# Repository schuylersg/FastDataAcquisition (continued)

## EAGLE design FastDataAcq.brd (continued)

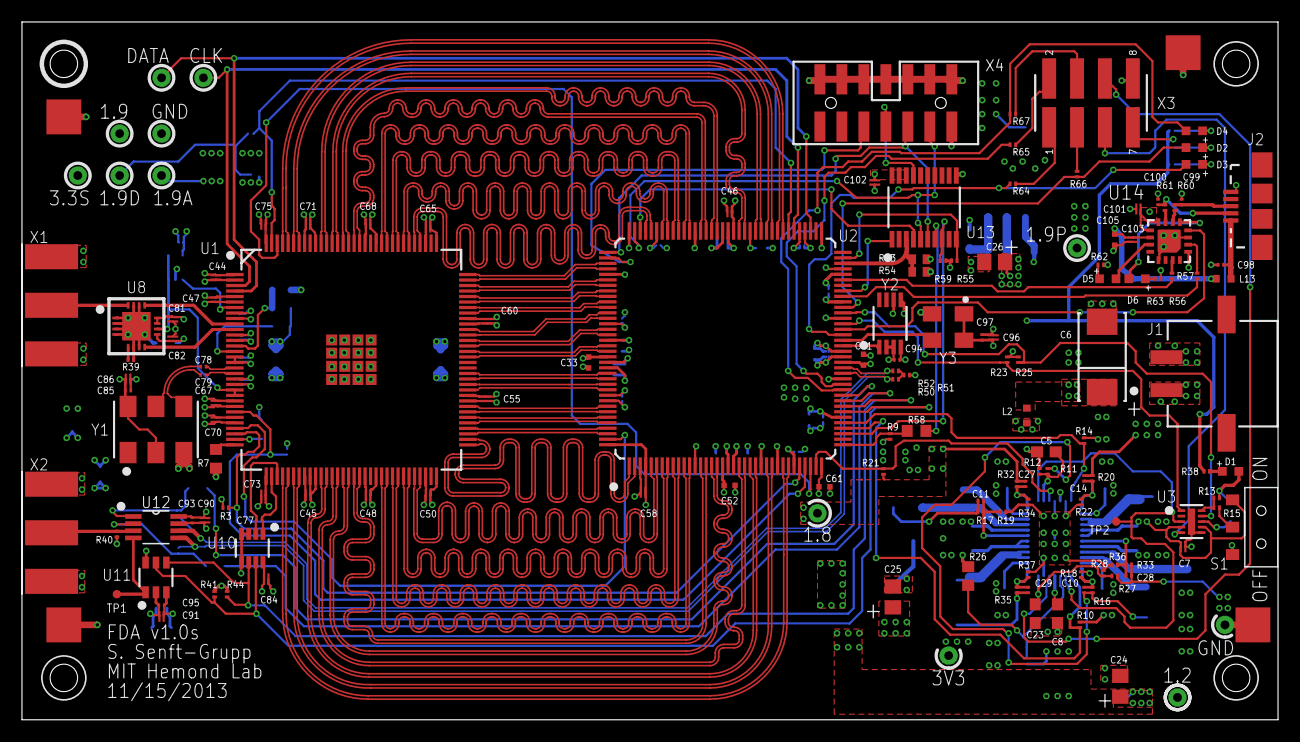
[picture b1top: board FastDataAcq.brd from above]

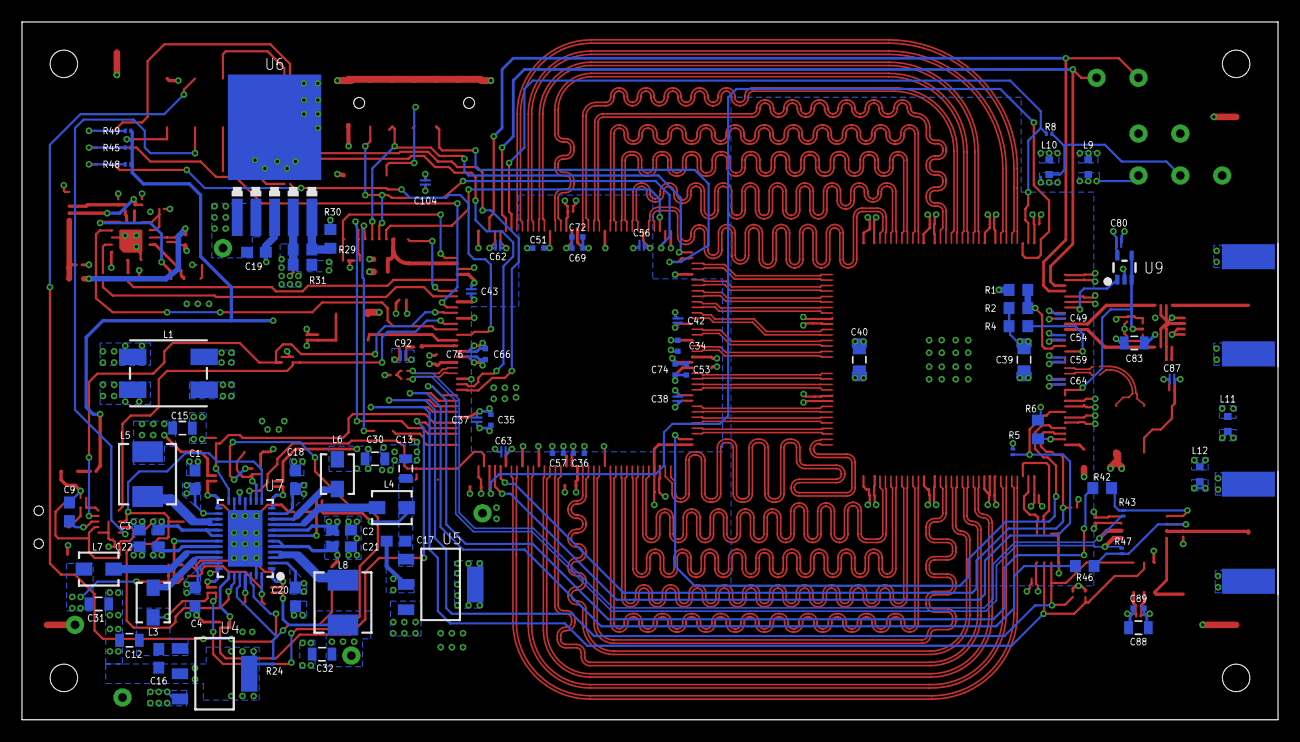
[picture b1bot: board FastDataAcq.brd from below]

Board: 4 copper layers, 114.3 x 63.5 mm, 225 parts (82 on the bottom side), 186 nets.

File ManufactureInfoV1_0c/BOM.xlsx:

Parts | Value | MFG PN | Digikey PN | SUPPLIER | Qty | Package | Description
C1, C2, C3, C4, C8, C16, C17, C18, C19, C20, C21, C22 | 10uF |  | 445-4112-1-ND | DIGIKEY | 12 | C0603 | CAPACITOR, European symbol
C10, C11, C14, C27, C28, C29 | 10pF |  | 445-1769-1-ND | DIGIKEY | 6 | C0201 | CAPACITOR, European symbol
C12, C13, C15, C30, C31, C32, C39, C40, C83, C88 | 33uF |  | 445-8238-1-ND | DIGIKEY | 10 | 805 | Capacitor
C24, C25, C26 | 22uF 150mOhm ESR |  | P16231CT-ND | DIGIKEY | 3 | C0805 | CAPACITOR, American symbol
C33, C34, C35, C36, C41, C51, C52, C53, C57, C61, C66, C69, C72, C74, C89, C105 | 4.7uF | CL05A475MQ5NRNC | 1276-1056-1-ND | DIGIKEY | 16 | 0402_C | Capacitors.
C37, C38, C42, C43, C46, C56, C58, C62, C63, C76 | 0.47uF |  | 1276-1779-1-ND | DIGIKEY | 10 | 0204REVERSE | Capacitors.
C5, C9, C23 | DNP |  |  |  | 3 | C0603 | CAPACITOR, European symbol
C6 | 100uF | ECASD91B107M012K00 | 490-5480-1-ND | DIGIKEY | 1 | 2917_MURATA_CAP | Polarized capacitors.
C7, C44, C45, C47, C48, C49, C50, C54, C55, C59, C60, C64, C65, C67, C68, C70, 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 | .1uF |  | 587-2152-1-ND | DIGIKEY | 30 | 0204REVERSE | Capacitors.
C77 | 100pF |  | 445-4675-1-ND | DIGIKEY | 1 | C0201 | CAPACITOR, European symbol
C78, C79 | 4.7nF |  | 445-13726-1-ND | DIGIKEY | 2 | C0201 | CAPACITOR, European symbol
C85, C93, C94, C95, C97, C98 | 10nF |  | 445-1793-1-ND | DIGIKEY | 6 | C0201 | CAPACITOR, European symbol
C87, C90, C104 | 1uF |  | 445-9091-1-ND | DIGIKEY | 3 | 0204REVERSE | Capacitors.
C99, C100 | 47pF |  | 445-1782-1-ND | DIGIKEY | 2 | C0201 | CAPACITOR, European symbol
D1, D4 | LED_0603_RED |  | LNJ237W82RACT-ND | DIGIKEY | 2 | 0603_LED | LED.
D2, D6 | LED_0603_BLUE | LTST-C193TBKT-5A | 160-1827-1-ND | DIGIKEY | 2 | 0603_LED | LED.
D3, D5 | LED_0603_GREEN | LTST-C193KGKT-5A | 160-1828-1-ND | DIGIKEY | 2 | 0603_LED | LED.
J1 | MICRO-FIT_3.0_2POS_RA_SMD | 436500212 | WM1890CT-ND | DIGIKEY | 1 | MICRO-FIT_3.02POS_RA_SMD
J2 | USB_MICROAB_SMT | 10104111-0001LF | 609-4053-1-ND | DIGIKEY | 1 | USB_MICROAB_SMT_1 | USB Connector
L1 | CHOKE_CM_ACM7060-301 | ACM7060-301-2PL-TL01 | 445-2214-1-ND | DIGIKEY | 1 | ACM7060_CHOKE | Common mode choke.
L13 | 330 | BLM18SG331TN1D | 490-3997-1-ND | DIGIKEY | 1 | MURATA_BLM18 | Ferrite bead.
L2, L9, L10, L11, L12 | 26 | BLM18SG260TN1D | 490-3995-1-ND | DIGIKEY | 5 | MURATA_BLM18 | Ferrite bead.
L3, L4, L6, L7 | 2.2uH |  | 541-1322-1-ND | DIGIKEY | 4 | 3.0X3.6_VISHAY | Inductors.
L5, L8 | 2.2uH |  | 541-1220-1-ND | DIGIKEY | 2 | 5.18X5.49_VISHAY | Inductors.
R1, R2, R4, R6, R26 | DNP |  |  |  | 5 | R0603 | RESISTOR, American symbol
R10, R13, R14, R16, R17, R20, R23, R24, R25 | 523K |  | P523KABCT-ND | DIGIKEY | 9 | R0201 | RESISTOR, American symbol
R11, R34 | 649K |  | P649KABCT-ND | DIGIKEY | 2 | R0201 | RESISTOR, American symbol
R12, R19 | 150K |  | 1276-3719-1-ND | DIGIKEY | 2 | R0201 | RESISTOR, American symbol
R15 | 113k |  | P113KABCT-ND | DIGIKEY | 1 | R0201 | RESISTOR, American symbol
R18, R28, R33 | 210K |  | P210KABCT-ND | DIGIKEY | 3 | R0201 | RESISTOR, American symbol
R22 | 280K |  | P280KABCT-ND | DIGIKEY | 1 | R0201 | RESISTOR, American symbol
R27, R37 | 270k |  | P270KABCT-ND | DIGIKEY | 2 | R0201 | RESISTOR, American symbol
R29 | 1.15k 1% | RC1608F1151CS | 1276-4649-1-ND | DIGIKEY | 1 | R0603 | RESISTOR, American symbol
R3, R5, R8, R21, R41, R43, R44, R47 | 10k | RC0603J103CS | 1276-3817-1-ND | DIGIKEY | 8 | R0201 | RESISTOR, American symbol
R30 | 2k 1% | RC1608F202CS | 1276-3495-1-ND | DIGIKEY | 1 | R0603 | RESISTOR, American symbol
R31 | 100 | RC1608J101CS | 1276-5038-1-ND | DIGIKEY | 1 | R0603 | RESISTOR, American symbol
R32 | 806K |  | P806KABCT-ND | DIGIKEY | 1 | R0201 | RESISTOR, American symbol
R35 | 845k |  | P845KABCT-ND | DIGIKEY | 1 | R0201 | RESISTOR, American symbol
R36 | 422K |  | P442KABCT-ND | DIGIKEY | 1 | R0201 | RESISTOR, American symbol
R38, R45, R48, R49, R55, R56, R57, R62, R63, R64, R65, R66, R67 | 330 | RC0603J331CS | 1276-3787-1-ND | DIGIKEY | 13 | R0201 | RESISTOR, American symbol
R39, R40, R50, R51, R52 | 50 | RC0603F49R9C | 1276-3590-1-ND | DIGIKEY | 5 | R0201 | RESISTOR, American symbol
R42 | 26.1k |  | 1276-4779-1-ND | DIGIKEY | 1 | R0603 | RESISTOR, American symbol
R46 | 16k |  | 1276-5091-1-ND | DIGIKEY | 1 | R0603 | RESISTOR, American symbol
R53, R54 | 100 0.1% | ERA-2AEB101X | P100DCCT-ND | DIGIKEY | 2 | R0402 | RESISTOR, American symbol
R58 | 0 |  | 311-0.0GRCT-ND | DIGIKEY | 1 | R0603 | RESISTOR, American symbol
R60, R61 | 27 |  | 1276-3577-1-ND | DIGIKEY | 2 | R0201 | RESISTOR, American symbol
R7 | 3.3k 0.1% |  | P3.3KDBCT-ND | DIGIKEY | 1 | R0603 | RESISTOR, American symbol
R9, R59 | 4.7k | ERJ-1GNJ472C | P4.7AECT-ND | DIGIKEY | 2 | R0201 | RESISTOR, American symbol
S1 | SLIDER_SPDT_AYZ0102AGRLC | AYZ0102AGRLC | 401-2012-1-ND | DIGIKEY | 1 | AYZ0102AGRLC | SPDT Slider switch from C&K Corp.
U1 | ADC08D500 | ADC08D500CIYB/NOPB | ADC08D500CIYB/NOPB-ND | DIGIKEY | 1 | 128HLQFP | TI ADC08D500 is a dual ADC running at 500MHz for a total of 1 GSPS. Verified=fa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
U10 | TMP421 | TMP421AIDCNT | 296-21990-1-ND | DIGIKEY | 1 | SOT23-8 | Remote and local temperature sensor (+/- 1C) from TI. TMP421. http://www.ti.com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
U11 | DAC101C081 | DAC101C081CIMK/NOPB | DAC101C081CIMK/NOPBCT-ND | DIGIKEY | 1 | SOT23-6 | 10-bit DAC from TI. http://www.ti.com/lit/ds/symlink/dac101c081.pdf
U12 | ADCMP553BRMZ | ADCMP553BRMZ | ADCMP553BRMZ-ND | DIGIKEY | 1 | SOP65P490X110-8N | PECL/LVPECL Comparators
U13 | XCFXXS04 | XCF04SVOG20C | 122-1288-5-ND | DIGIKEY | 1 | TSSOP20_XILINX | XCFxxS Xilinx Program Flash.
U14 | FT230XQ | FT230XQ-R | 768-1130-1-ND | DIGIKEY | 1 | QFN16 | USB to BASIC UART IC
U2 | XC6SLX9-3TQG144C | XC6SLX9-3TQG144C | 122-1747-ND | DIGIKEY | 1 | TQG144 | Xilinx Spartan 6 LX9 FPGA in the TQG144 package.
U3 | LTC2955-1 | LTC2955CDDB-1#TRMPBF | LTC2955CDDB-1#TRMPBFCT-ND | DIGIKEY | 1 | 10-DFN | Pushbutton On/Off Controller with Automatic Turn-On
U4 | LT1963AEST-2.5 | LT1963AEST-2.5#PBF | LT1963AEST-2.5#PBF-ND | DIGIKEY | 1 | SOT223 | LT1963A Series LDO in a 3 Lead SOT223 package. http://cds.linear.com/docs/en/da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
U5 | LT1963AEST-3.3 | LT1963AEST-3.3#PBF | LT1963AEST-3.3#PBF-ND | DIGIKEY | 1 | SOT223 | LT1963A Series LDO in a 3 Lead SOT223 package. http://cds.linear.com/docs/en/da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
U6 | LT1963AEQ | LT1963AEQ#PBF | LT1963AEQ#PBF-ND | DIGIKEY | 1 | Q5-DD | LT1963 1.5A, Low Noise, Fast Transient Response LDO Regulator
U7 | LTC3374QFN | TC3374EUHF#PBF | LTC3374EUHF#PBF-ND | DIGIKEY | 1 | 38-QFN_(5X7) | LTC3374 8-Channel 1A Buck DC-DC Regulator. http://cds.linear.com/docs/en/datash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
U8 | LMH6555 | LMH6555SQ/NOPB | LMH6555SQ/NOPBCT-ND | DIGIKEY | 1 | 16WQFN | LMH6555 is a low distortion 1.2 GHz differential driver. It can be configured f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
U9 | LMV321SC-70 | LMV321IDCKR | 296-9568-1-ND | DIGIKEY | 1 | SC-70 | LMV321 Low Voltage Rail-to-rail op amp from TI. Verified=false.
X1, X2 | SMA-142-0701-801/806 | 142-0701-801 | J502-ND | DIGIKEY | 2 | J502-ND-142-0701-801/806 | SMA 50 Ohm End Launch Jack Receptacle - Round Contact
X3 | HEADER_0.1_8P_2R_SMT" | 15912080 | WM17450-ND | DIGIKEY | 1 | HEADER_8P_2R_SMT
X4 | 87832-14 | 878321420 | WM18641-ND | DIGIKEY | 1 | 87832-14 | Milli-Grid Header
Y1 | SI530-500 | 530FC500M000DG | 530FC500M000DG | SILICON LABS | 1 | SI530 | Crystal Oscillator from Silicon Labs. Factory progrramed between 0.01 and 1.4 G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
Y2 | 100MHz | DS1088LU-100+ | DS1088LU-100+-ND | DIGIKEY | 1 | UMAX8 | MAXIM DS1088L Fixed frequency EconOscillator. Factory programmed between 321kHz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
Y3 | DNP | 500SAAA-ACF | 500SAAA-ACF-ND | DIGIKEY | 1 | SI500S | Silicon Labs SI500S programmable oscillator. https://www.silabs.com/Support%20D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

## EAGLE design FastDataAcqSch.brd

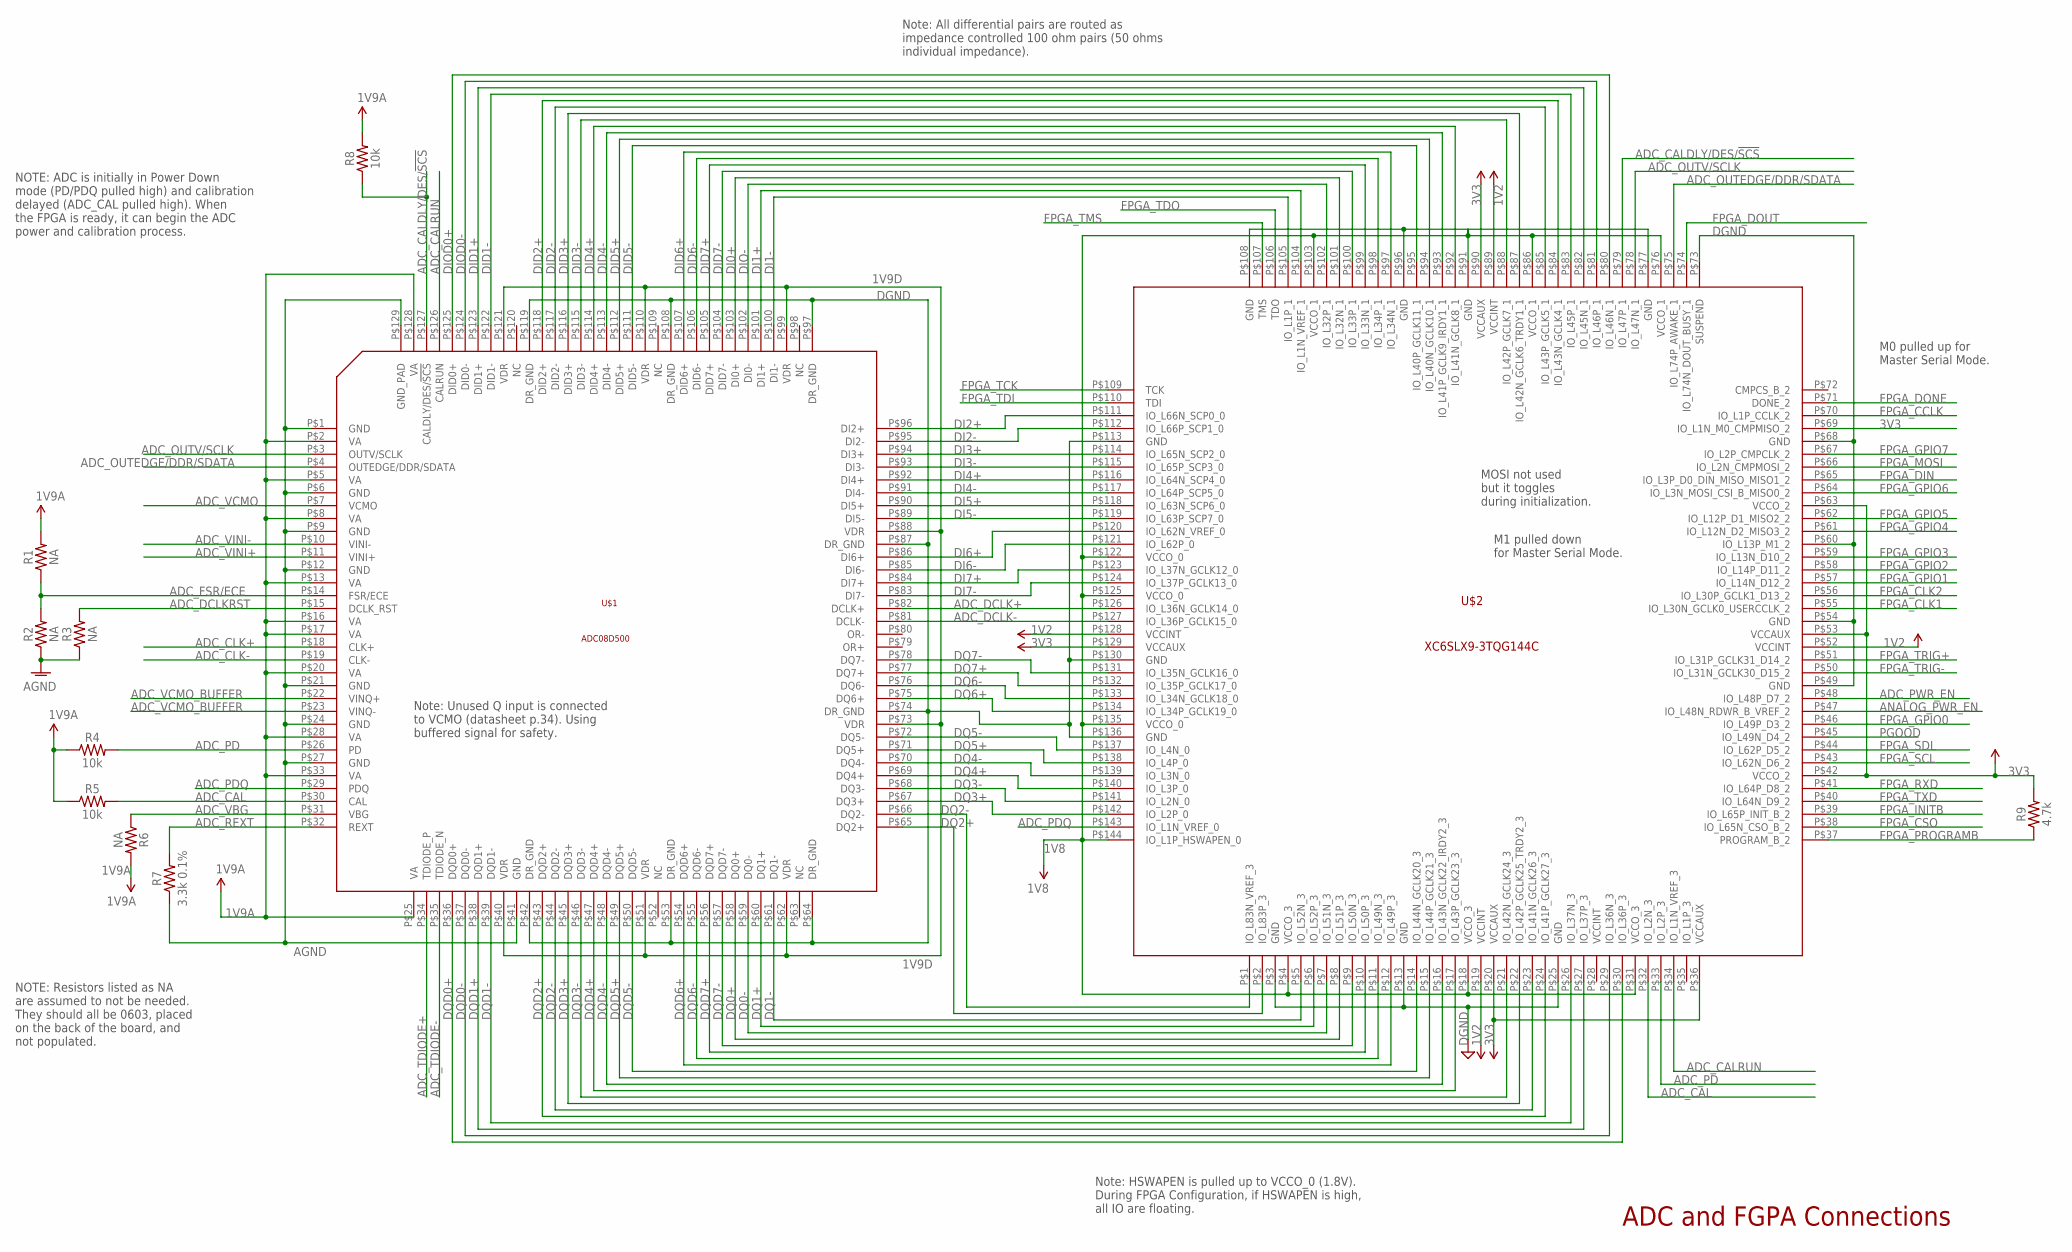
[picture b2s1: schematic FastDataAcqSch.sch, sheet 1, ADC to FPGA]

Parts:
R1, R2, R3, R6: NA; R0603
R4, R5, R8: 10k; R0201; MANPARTNUMBER RC0603J103CS
R7: 3.3k 0.1%; R0603; PARTNUMBER P3.3KDBCT-ND
R9: 4.7k; R0201; MANPARTNUMBER ERJ-1GNJ472C
U$1: ADC08D500; 128HLQFP; PARTNUMBER ADC08D500CIYB/NOPB-ND
U$2: XC6SLX9-3TQG144C; TQG144

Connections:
1V2: U$2.P$52 (VCCINT), U$2.P$89 (VCCINT), U$2.P$128 (VCCINT); also elsewhere on the board
1V8: U$2.P$4 (VCCO_3), U$2.P$18 (VCCO_3), U$2.P$31 (VCCO_3), U$2.P$76 (VCCO_1), U$2.P$77 (GND), U$2.P$86 (VCCO_1), U$2.P$103 (VCCO_1), U$2.P$122 (VCCO_0), U$2.P$125 (VCCO_0), U$2.P$135 (VCCO_0), U$2.P$144 (IO_L1P_HSWAPEN_0); also elsewhere on the board
1V9A: R1.2, R4.1, R5.1, R6.2, R8.2, U$1.P$2 (VA), U$1.P$5 (VA), U$1.P$8 (VA), U$1.P$13 (VA), U$1.P$16 (VA), U$1.P$17 (VA), U$1.P$20 (VA), U$1.P$25 (VA), U$1.P$28 (VA), U$1.P$33 (VA), U$1.P$128 (VA); also elsewhere on the board
1V9D: U$1.P$40 (VDR), U$1.P$51 (VDR), U$1.P$62 (VDR), U$1.P$73 (VDR), U$1.P$88 (VDR), U$1.P$99 (VDR), U$1.P$110 (VDR), U$1.P$121 (VDR); also elsewhere on the board
3V3: R9.2, U$2.P$36 (VCCAUX), U$2.P$42 (VCCO_2), U$2.P$53 (VCCAUX), U$2.P$63 (VCCO_2), U$2.P$69 (IO_L1N_M0_CMPMISO_2), U$2.P$90 (VCCAUX), U$2.P$129 (VCCAUX); also elsewhere on the board
ADC_CAL: R5.2, U$1.P$30 (CAL), U$2.P$32 (IO_L2N_3)
ADC_CALDLY/DES/!SCS: R8.1, U$1.P$127 (CALDLY/DES/!SCS), U$2.P$79 (IO_L47P_1)
ADC_CALRUN: U$1.P$126 (CALRUN), U$2.P$34 (IO_L1N_VREF_3)
ADC_CLK+: U$1.P$18 (CLK+); also elsewhere on the board
ADC_CLK-: U$1.P$19 (CLK-); also elsewhere on the board
ADC_DCLK+: U$1.P$82 (DCLK+), U$2.P$126 (IO_L36N_GCLK14_0)
ADC_DCLK-: U$1.P$81 (DCLK-), U$2.P$127 (IO_L36P_GCLK15_0)
ADC_DCLKRST: R3.2, U$1.P$15 (DCLK_RST)
ADC_FSR/ECE: R1.1, R2.2, U$1.P$14 (FSR/ECE)
ADC_OUTEDGE/DDR/SDATA: U$1.P$4 (OUTEDGE/DDR/SDATA), U$2.P$75 (IO_L74P_AWAKE_1)
ADC_OUTV/SCLK: U$1.P$3 (OUTV/SCLK), U$2.P$78 (IO_L47N_1)
ADC_PD: R4.2, U$1.P$26 (PD), U$2.P$33 (IO_L2P_3)
ADC_PDQ: U$1.P$29 (PDQ), U$2.P$143 (IO_L1N_VREF_0)
ADC_PWR_EN: U$2.P$48 (IO_L48P_D7_2); also elsewhere on the board
ADC_REXT: R7.2, U$1.P$32 (REXT)
ADC_TDIODE+: U$1.P$34 (TDIODE_P); also elsewhere on the board
ADC_TDIODE-: U$1.P$35 (TDIODE_N); also elsewhere on the board
ADC_VBG: R6.1, U$1.P$31 (VBG)
ADC_VCMO: U$1.P$7 (VCMO); also elsewhere on the board
ADC_VCMO_BUFFER: U$1.P$22 (VINQ+), U$1.P$23 (VINQ-); also elsewhere on the board
ADC_VINI+: U$1.P$11 (VINI+); also elsewhere on the board
ADC_VINI-: U$1.P$10 (VINI-); also elsewhere on the board
AGND: R2.1, R3.1, R7.1, U$1.P$1 (GND), U$1.P$6 (GND), U$1.P$9 (GND), U$1.P$12 (GND), U$1.P$21 (GND), U$1.P$24 (GND), U$1.P$27 (GND), U$1.P$41 (GND), U$1.P$129 (GND_PAD); also elsewhere on the board
ANALOG_PWR_EN: U$2.P$47 (IO_L48N_RDWR_B_VREF_2); also elsewhere on the board
DGND: U$1.P$42 (DR_GND), U$1.P$53 (DR_GND), U$1.P$64 (DR_GND), U$1.P$74 (DR_GND), U$1.P$87 (DR_GND), U$1.P$97 (DR_GND), U$1.P$108 (DR_GND), U$1.P$119 (DR_GND), U$2.P$3 (GND), U$2.P$13 (GND), U$2.P$25 (GND), U$2.P$49 (GND), U$2.P$54 (GND), U$2.P$60 (IO_L13P_M1_2), U$2.P$68 (GND), U$2.P$73 (SUSPEND), U$2.P$113 (GND), U$2.P$130 (GND), U$2.P$136 (GND); also elsewhere on the board
DI0+: U$1.P$103 (DI0+), U$2.P$101 (IO_L32N_1)
DI1+: U$1.P$101 (DI1+), U$2.P$104 (IO_L1N_VREF_1)
DI1-: U$1.P$100 (DI1-), U$2.P$105 (IO_L1P_1)
DI2+: U$1.P$96 (DI2+), U$2.P$111 (IO_L66N_SCP0_0)
DI2-: U$1.P$95 (DI2-), U$2.P$112 (IO_L66P_SCP1_0)
DI3+: U$1.P$94 (DI3+), U$2.P$114 (IO_L65N_SCP2_0)
DI3-: U$1.P$93 (DI3-), U$2.P$115 (IO_L65P_SCP3_0)
DI4+: U$1.P$92 (DI4+), U$2.P$116 (IO_L64N_SCP4_0)
DI4-: U$1.P$91 (DI4-), U$2.P$117 (IO_L64P_SCP5_0)
DI5+: U$1.P$90 (DI5+), U$2.P$118 (IO_L63N_SCP6_0)
DI5-: U$1.P$89 (DI5-), U$2.P$119 (IO_L63P_SCP7_0)
DI6+: U$1.P$86 (DI6+), U$2.P$120 (IO_L62N_VREF_0)
DI6-: U$1.P$85 (DI6-), U$2.P$121 (IO_L62P_0)
DI7+: U$1.P$84 (DI7+), U$2.P$123 (IO_L37N_GCLK12_0)
DI7-: U$1.P$83 (DI7-), U$2.P$124 (IO_L37P_GCLK13_0)
DID1+: U$1.P$123 (DID1+), U$2.P$82 (IO_L45N_1)
DID1-: U$1.P$122 (DID1-), U$2.P$83 (IO_L45P_1)
DID2+: U$1.P$118 (DID2+), U$2.P$84 (IO_L43N_GCLK4_1)
DID2-: U$1.P$117 (DID2-), U$2.P$85 (IO_L43P_GCLK5_1)
DID3+: U$1.P$116 (DID3+), U$2.P$87 (IO_L42N_GCLK6_TRDY1_1)
DID3-: U$1.P$115 (DID3-), U$2.P$88 (IO_L42P_GCLK7_1)
DID4+: U$1.P$114 (DID4+), U$2.P$92 (IO_L41N_GCLK8_1)
DID4-: U$1.P$113 (DID4-), U$2.P$93 (IO_L41P_GCLK9_IRDY1_1)
DID5+: U$1.P$112 (DID5+), U$2.P$94 (IO_L40N_GCLK10_1)
DID5-: U$1.P$111 (DID5-), U$2.P$95 (IO_L40P_GCLK11_1)
DID6+: U$1.P$107 (DID6+), U$2.P$97 (IO_L34N_1)
DID6-: U$1.P$106 (DID6-), U$2.P$98 (IO_L34P_1)
DID7+: U$1.P$105 (DID7+), U$2.P$99 (IO_L33N_1)
DID7-: U$1.P$104 (DID7-), U$2.P$100 (IO_L33P_1)
DIO-: U$1.P$102 (DI0-), U$2.P$102 (IO_L32P_1)
DIOD0+: U$1.P$125 (DID0+), U$2.P$80 (IO_L46N_1)
DIOD0-: U$1.P$124 (DID0-), U$2.P$81 (IO_L46P_1)
DQ0+: U$1.P$58 (DQ0+), U$2.P$8 (IO_L51P_3)
DQ0-: U$1.P$59 (DQ0-), U$2.P$7 (IO_L51N_3)
DQ1+: U$1.P$60 (DQ1+), U$2.P$6 (IO_L52P_3)
DQ1-: U$1.P$61 (DQ1-), U$2.P$5 (IO_L52N_3)
DQ2+: U$1.P$65 (DQ2+), U$2.P$2 (IO_L83P_3)
DQ2-: U$1.P$66 (DQ2-), U$2.P$1 (IO_L83N_VREF_3)
DQ3+: U$1.P$67 (DQ3+), U$2.P$142 (IO_L2P_0)
DQ3-: U$1.P$68 (DQ3-), U$2.P$141 (IO_L2N_0)
DQ4+: U$1.P$69 (DQ4+), U$2.P$140 (IO_L3P_0)
DQ4-: U$1.P$70 (DQ4-), U$2.P$139 (IO_L3N_0)
DQ5+: U$1.P$71 (DQ5+), U$2.P$138 (IO_L4P_0)
DQ5-: U$1.P$72 (DQ5-), U$2.P$137 (IO_L4N_0)
DQ6+: U$1.P$75 (DQ6+), U$2.P$134 (IO_L34P_GCLK19_0)
DQ6-: U$1.P$76 (DQ6-), U$2.P$133 (IO_L34N_GCLK18_0)
DQ7+: U$1.P$77 (DQ7+), U$2.P$132 (IO_L35P_GCLK17_0)
DQ7-: U$1.P$78 (DQ7-), U$2.P$131 (IO_L35N_GCLK16_0)
DQD0+: U$1.P$36 (DQD0+), U$2.P$30 (IO_L36P_3)
DQD0-: U$1.P$37 (DQD0-), U$2.P$29 (IO_L36N_3)
DQD1+: U$1.P$38 (DQD1+), U$2.P$27 (IO_L37P_3)
DQD1-: U$1.P$39 (DQD1-), U$2.P$26 (IO_L37N_3)
DQD2+: U$1.P$43 (DQD2+), U$2.P$24 (IO_L41P_GCLK27_3)
DQD2-: U$1.P$44 (DQD2-), U$2.P$23 (IO_L41N_GCLK26_3)
DQD3+: U$1.P$45 (DQD3+), U$2.P$22 (IO_L42P_GCLK25_TRDY2_3)
DQD3-: U$1.P$46 (DQD3-), U$2.P$21 (IO_L42N_GCLK24_3)
DQD4+: U$1.P$47 (DQD4+), U$2.P$17 (IO_L43P_GCLK23_3)
DQD4-: U$1.P$48 (DQD4-), U$2.P$16 (IO_L43N_GCLK22_IRDY2_3)
DQD5+: U$1.P$49 (DQD5+), U$2.P$15 (IO_L44P_GCLK21_3)
DQD5-: U$1.P$50 (DQD5-), U$2.P$14 (IO_L44N_GCLK20_3)
DQD6+: U$1.P$54 (DQD6+), U$2.P$12 (IO_L49P_3)
DQD6-: U$1.P$55 (DQD6-), U$2.P$11 (IO_L49N_3)
DQD7+: U$1.P$56 (DQD7+), U$2.P$10 (IO_L50P_3)
DQD7-: U$1.P$57 (DQD7-), U$2.P$9 (IO_L50N_3)
FPGA_CCLK: U$2.P$70 (IO_L1P_CCLK_2); also elsewhere on the board
FPGA_CLK1: U$2.P$55 (IO_L30N_GCLK0_USERCCLK_2); also elsewhere on the board
FPGA_CLK2: U$2.P$56 (IO_L30P_GCLK1_D13_2); also elsewhere on the board
FPGA_CSO: U$2.P$38 (IO_L65N_CSO_B_2)
FPGA_DIN: U$2.P$65 (IO_L3P_D0_DIN_MISO_MISO1_2); also elsewhere on the board
FPGA_DONE: U$2.P$71 (DONE_2); also elsewhere on the board
FPGA_DOUT: U$2.P$74 (IO_L74N_DOUT_BUSY_1)
FPGA_GPIO0: U$2.P$46 (IO_L49P_D3_2); also elsewhere on the board
FPGA_GPIO1: U$2.P$57 (IO_L14N_D12_2); also elsewhere on the board
FPGA_GPIO2: U$2.P$58 (IO_L14P_D11_2); also elsewhere on the board
FPGA_GPIO3: U$2.P$59 (IO_L13N_D10_2); also elsewhere on the board
FPGA_GPIO4: U$2.P$61 (IO_L12N_D2_MISO3_2); also elsewhere on the board
FPGA_GPIO5: U$2.P$62 (IO_L12P_D1_MISO2_2); also elsewhere on the board
FPGA_GPIO6: U$2.P$64 (IO_L3N_MOSI_CSI_B_MISO0_2); also elsewhere on the board
FPGA_GPIO7: U$2.P$67 (IO_L2P_CMPCLK_2); also elsewhere on the board
FPGA_INITB: U$2.P$39 (IO_L65P_INIT_B_2); also elsewhere on the board
FPGA_MOSI: U$2.P$66 (IO_L2N_CMPMOSI_2)
FPGA_PROGRAMB: R9.1, U$2.P$37 (PROGRAM_B_2); also elsewhere on the board
FPGA_RXD: U$2.P$41 (IO_L64P_D8_2); also elsewhere on the board
FPGA_SCL: U$2.P$43 (IO_L62N_D6_2); also elsewhere on the board
FPGA_SDL: U$2.P$44 (IO_L62P_D5_2)
FPGA_TCK: U$2.P$109 (TCK); also elsewhere on the board
FPGA_TDI: U$2.P$110 (TDI); also elsewhere on the board
FPGA_TDO: U$2.P$106 (TDO); also elsewhere on the board
FPGA_TMS: U$2.P$107 (TMS); also elsewhere on the board
FPGA_TRIG+: U$2.P$51 (IO_L31P_GCLK31_D14_2); also elsewhere on the board
FPGA_TRIG-: U$2.P$50 (IO_L31N_GCLK30_D15_2); also elsewhere on the board
FPGA_TXD: U$2.P$40 (IO_L64N_D9_2); also elsewhere on the board
unnamed: U$2.P$91 (GND), U$2.P$96 (GND), U$2.P$108 (GND)
PGOOD: U$2.P$45 (IO_L49N_D4_2); also elsewhere on the board
VCCAUX: U$2.P$20 (VCCAUX)
VCCINT: U$2.P$19 (VCCINT), U$2.P$28 (VCCINT)

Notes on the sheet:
ADC and FGPA Connections
Note: Unused Q input is connected to VCMO (datasheet p.34). Using buffered signal for safety.
MOSI not used but it toggles during initialization.
M0 pulled up for Master Serial Mode.
M1 pulled down for Master Serial Mode.
Note: HSWAPEN is pulled up to VCCO_0 (1.8V). During FPGA Configuration, if HSWAPEN is high, all IO are floating.
NOTE: Resistors listed as NA are assumed to not be needed. They should all be 0603, placed on the back of the board, and not populated.
NOTE: ADC is initially in Power Down mode (PD/PDQ pulled high) and calibration delayed (ADC_CAL pulled high). When the FPGA is ready, it can begin the ADC power and calibration process.
Note: All differential pairs are routed as impedance controlled 100 ohm pairs (50 ohms individual impedance).

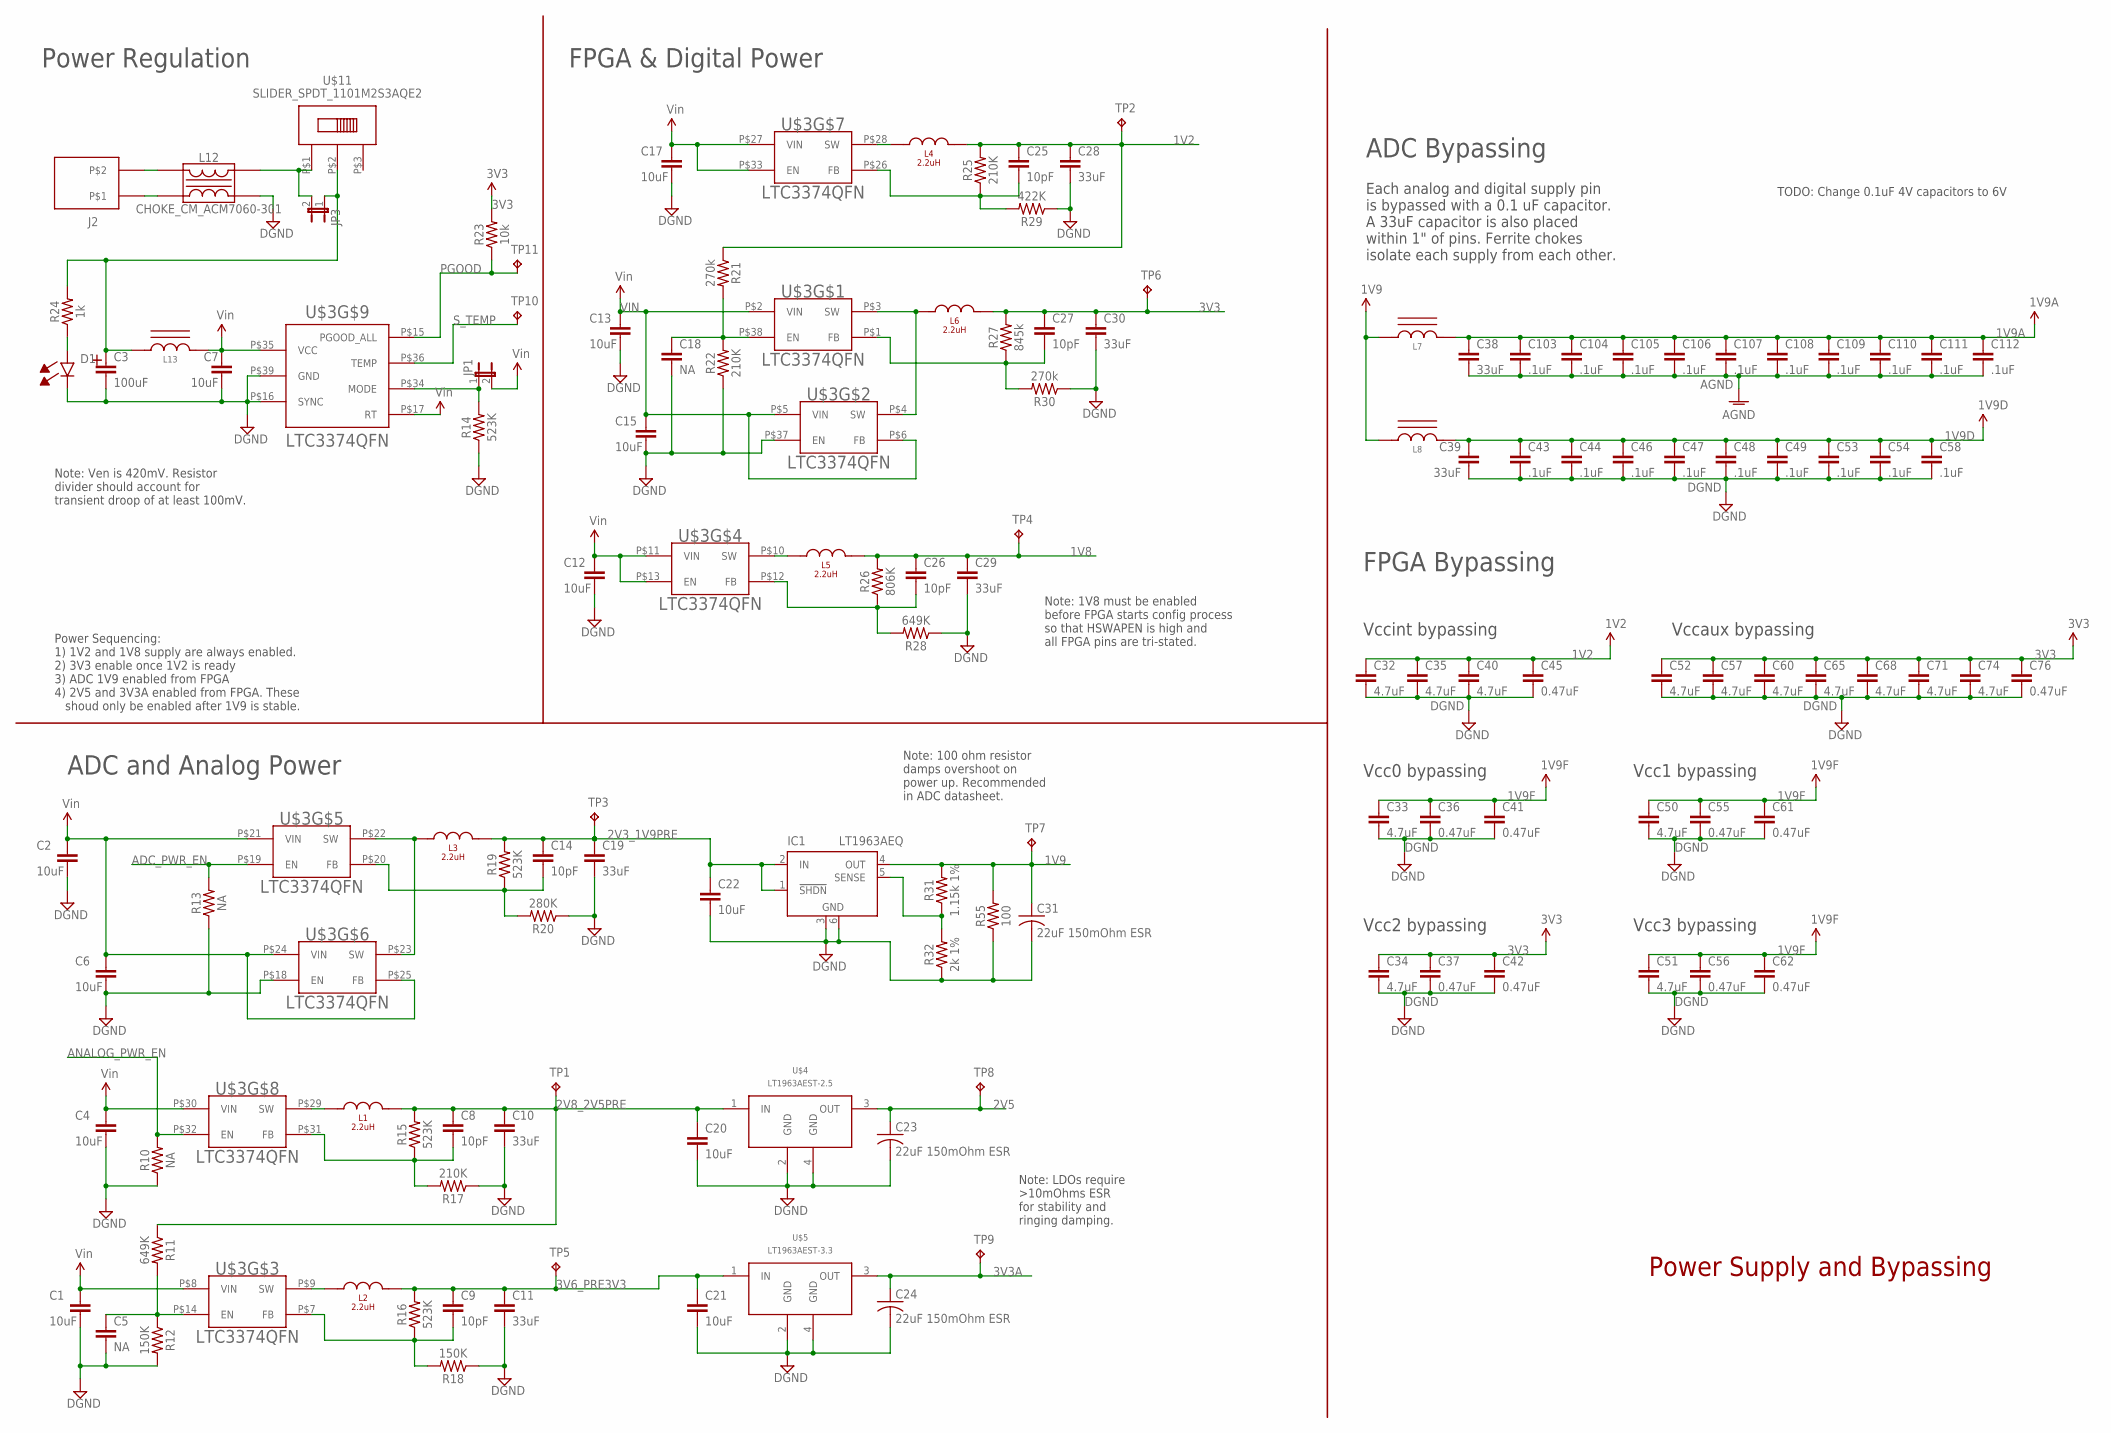
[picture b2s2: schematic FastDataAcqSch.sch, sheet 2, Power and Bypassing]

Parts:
C1, C2, C4, C6, C7, C12, C13, C15, C17, C20, C21, C22: 10uF; C0603; PARTNUMBER 445-4112-1-ND
C3: 100uF; 2917_MURATA_CAP; MANPARTNUMBER ECASD91B107M012K00
C5, C18: NA; C0603
C8, C9, C14, C25, C26, C27: 10pF; C0201; PARTNUMBER 445-1769-1-ND
C10, C11, C19, C28, C29, C30, C38, C39: 33uF; 0805; PARTNUMBER 445-8238-1-ND
C23, C24, C31: 22uF 150mOhm ESR; C0805; PARTNUMBER P16231CT-ND
C32, C33, C34, C35, C40, C50, C51, C52, C57, C60, C65, C68, C71, C74: 4.7uF; 0306REVERSE; PARTNUMBER 445-13745-1-ND
C36, C37, C41, C42, C45, C55, C56, C61, C62, C76: 0.47uF; 0306REVERSE; PARTNUMBER 445-13744-1-ND
C43, C44, C46, C47, C48, C49, C53, C54, C58, C103, C104, C105, C106, C107, C108, C109, C110, C111, C112: .1uF; 0204REVERSE; PARTNUMBER 587-2152-1-ND
D1: LED_0603_RED; 0603_LED
IC1: LT1963AEQ; Q5-DD; MANPARTNUMBER LT1963AEQ#PBF
J2: MICRO-FIT_3.0_2POS_RA_SMD; MICRO-FIT_3.02POS_RA_SMD
JP1, JP3: JUMPER-2PTH; 1X02
L1, L2, L4, L5: 2.2uH; 3.0X3.6_VISHAY; PARTNUMBER 541-1322-1-ND
L3, L6: 2.2uH; 5.18X5.49_VISHAY; PARTNUMBER 541-1220-1-ND
L7, L8, L13: FERRITE_BEADS_BLM18SG260; MURATA_BLM18
L12: CHOKE_CM_ACM7060-301; ACM7060_CHOKE
R10, R13: NA; R0603
R11, R28: 649K; R0201; PARTNUMBER P649KABCT-ND
R12, R18: 150K; R0201; PARTNUMBER 1276-3719-1-ND
R14, R15, R16, R19: 523K; R0201; PARTNUMBER P523KABCT-ND
R17, R22, R25: 210K; R0201; PARTNUMBER P210KABCT-ND
R20: 280K; R0201; PARTNUMBER P280KABCT-ND
R21, R30: 270k; R0201; PARTNUMBER P270KABCT-ND
R23: 10k; R0201; MANPARTNUMBER RC0603J103CS
R24: 1k; R0201; PARTNUMBER 1276-3797-1-ND
R26: 806K; R0201; PARTNUMBER P806KABCT-ND
R27: 845k; R0201; PARTNUMBER P845KABCT-ND
R29: 422K; R0201; PARTNUMBER P442KABCT-ND
R31: 1.15k 1%; R0603; MANPARTNUMBER RC1608F1151CS
R32: 2k 1%; R0603; MANPARTNUMBER RC1608F202CS
R55: 100; R0603; MANPARTNUMBER RC1608J101CS
TP1, TP2, TP3, TP4, TP5, TP6, TP7, TP8, TP9, TP10, TP11: TPPAD1-13; P1-13
U$3: LTC3374QFN; 38-QFN_(5X7)
U$4: LT1963AEST-2.5; SOT223
U$5: LT1963AEST-3.3; SOT223
U$11: SLIDER_SPDT_1101M2S3AQE2; C_AND_K_1101M2S3AQE2

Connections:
1V2: C25.1, C28.1, C32.P$1 (1), C35.P$1 (1), C40.P$1 (1), C45.P$1 (1), L4.P$2, R21.1, R25.2, TP2.TP; also elsewhere on the board
1V8: C26.1, C29.1, L5.P$2, R26.2, TP4.TP; also elsewhere on the board
1V9: C31.1, IC1.4 (OUT), L7.P$1, L8.P$1, R31.2, R55.2, TP7.TP
1V9A: C38.1, C103.P$1 (1), C104.P$1 (1), C105.P$1 (1), C106.P$1 (1), C107.P$1 (1), C108.P$1 (1), C109.P$1 (1), C110.P$1 (1), C111.P$1 (1), C112.P$1 (1), L7.P$2; also elsewhere on the board
1V9D: C39.1, C43.P$1 (1), C44.P$1 (1), C46.P$1 (1), C47.P$1 (1), C48.P$1 (1), C49.P$1 (1), C53.P$1 (1), C54.P$1 (1), C58.P$1 (1), L8.P$2; also elsewhere on the board
1V9F: C33.P$1 (1), C36.P$1 (1), C41.P$1 (1), C50.P$1 (1), C51.P$1 (1), C55.P$1 (1), C56.P$1 (1), C61.P$1 (1), C62.P$1 (1)
2V3_1V9PRE: C14.1, C19.1, C22.1, IC1.1 (!SHDN), IC1.2 (IN), L3.P$2, R19.2, TP3.TP
2V5: C23.1, TP8.TP, U$4.3 (OUT); also elsewhere on the board
2V8_2V5PRE: C8.1, C10.1, C20.1, L1.P$2, R11.1, R15.2, TP1.TP, U$4.1 (IN)
3V3: C27.1, C30.1, C34.P$1 (1), C37.P$1 (1), C42.P$1 (1), C52.P$1 (1), C57.P$1 (1), C60.P$1 (1), C65.P$1 (1), C68.P$1 (1), C71.P$1 (1), C74.P$1 (1), C76.P$1 (1), L6.P$2, R27.2, TP6.TP; also elsewhere on the board
3V3A: C24.1, TP9.TP, U$5.3 (OUT); also elsewhere on the board
3V6_PRE3V3: C9.1, C11.1, C21.1, L2.P$2, R16.2, TP5.TP, U$5.1 (IN)
ADC_PWR_EN: R13.2, U$3.P$19 (EN); also elsewhere on the board
AGND: C38.2, C103.P$2 (2), C104.P$2 (2), C105.P$2 (2), C106.P$2 (2), C107.P$2 (2), C108.P$2 (2), C109.P$2 (2), C110.P$2 (2), C111.P$2 (2), C112.P$2 (2); also elsewhere on the board
ANALOG_PWR_EN: R10.2, U$3.P$32 (EN); also elsewhere on the board
DGND: C1.2, C2.2, C3.P$1 (NEG), C4.2, C5.2, C6.2, C7.2, C10.2, C11.2, C12.2, C13.2, C15.2, C17.2, C18.2, C19.2, C20.2, C21.2, C22.2, C23.2, C24.2, C28.2, C29.2, C30.2, C31.2, C32.P$2 (2), C33.P$2 (2), C34.P$2 (2), C35.P$2 (2), C36.P$2 (2), C37.P$2 (2), C39.2, C40.P$2 (2), C41.P$2 (2), C42.P$2 (2), C43.P$2 (2), C44.P$2 (2), C45.P$2 (2), C46.P$2 (2), C47.P$2 (2), C48.P$2 (2), C49.P$2 (2), C50.P$2 (2), C51.P$2 (2), C52.P$2 (2), C53.P$2 (2), C54.P$2 (2), C55.P$2 (2), C56.P$2 (2), C57.P$2 (2), C58.P$2 (2), C60.P$2 (2), C61.P$2 (2), C62.P$2 (2), C65.P$2 (2), C68.P$2 (2), C71.P$2 (2), C74.P$2 (2), C76.P$2 (2), D1.CATHODE, IC1.3 (GND), IC1.6 (GND), L12.P$3, R10.1, R12.2, R13.1, R14.1, R17.1, R18.1, R20.1, R22.1, R28.1, R29.1, R30.1, R32.1, R55.1, U$3.P$16 (SYNC), U$3.P$18 (EN), U$3.P$37 (EN), U$3.P$39 (GND), U$4.2 (GND), U$4.4 (GND), U$5.2 (GND), U$5.4 (GND); also elsewhere on the board
unnamed: JP3.2, L12.P$4, U$11.P$1
unnamed: JP1.1, R14.2, U$3.P$34 (MODE)
unnamed: D1.ANODE, R24.1
unnamed: C18.1, R21.2, R22.2, U$3.P$38 (EN)
unnamed: IC1.5 (SENSE), R31.1, R32.2
unnamed: C5.1, R11.2, R12.1, U$3.P$14 (EN)
unnamed: C3.P$2 (POS), JP3.1, L13.P$1, R24.2, U$11.P$2
PGOOD: R23.1, TP11.TP, U$3.P$15 (PGOOD_ALL); also elsewhere on the board
POWER_IN+: J2.P$2, L12.P$1
POWER_IN-: J2.P$1, L12.P$2
S1FB: C27.2, R27.1, R30.2, U$3.P$1 (FB)
S1SW: L6.P$1, U$3.P$3 (SW), U$3.P$4 (SW)
S3FB: C9.2, R16.1, R18.2, U$3.P$7 (FB)
S3SW: L2.P$1, U$3.P$9 (SW)
S4FB: C26.2, R26.1, R28.2, U$3.P$12 (FB)
S4SW: L5.P$1, U$3.P$10 (SW)
S5FB: C14.2, R19.1, R20.2, U$3.P$20 (FB)
S5SW: L3.P$1, U$3.P$22 (SW), U$3.P$23 (SW)
S7FB: C25.2, R25.1, R29.2, U$3.P$26 (FB)
S7SW: L4.P$1, U$3.P$28 (SW)
S8FB: C8.2, R15.1, R17.2, U$3.P$31 (FB)
S8SW: L1.P$1, U$3.P$29 (SW)
S_TEMP: TP10.TP, U$3.P$36 (TEMP)
VCC: JP1.2
VIN: C1.1, C2.1, C4.1, C6.1, C7.1, C12.1, C13.1, C15.1, C17.1, L13.P$2, U$3.P$2 (VIN), U$3.P$5 (VIN), U$3.P$6 (FB), U$3.P$8 (VIN), U$3.P$11 (VIN), U$3.P$13 (EN), U$3.P$17 (RT), U$3.P$21 (VIN), U$3.P$24 (VIN), U$3.P$25 (FB), U$3.P$27 (VIN), U$3.P$30 (VIN), U$3.P$33 (EN), U$3.P$35 (VCC)

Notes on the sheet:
Power Supply and Bypassing
ADC Bypassing
Each analog and digital supply pin is bypassed with a 0.1 uF capacitor. A 33uF capacitor is also placed within 1" of pins. Ferrite chokes isolate each supply from each other.
FPGA Bypassing
Vccint bypassing
Vccaux bypassing
Vcc0 bypassing
Vcc1 bypassing
Vcc2 bypassing
Vcc3 bypassing
TODO: Change 0.1uF 4V capacitors to 6V
Note: Ven is 420mV. Resistor divider should account for transient droop of at least 100mV.
Power Regulation
FPGA & Digital Power
ADC and Analog Power
Note: LDOs require >10mOhms ESR for stability and ringing damping.
Power Sequencing: 1) 1V2 and 1V8 supply are always enabled. 2) 3V3 enable once 1V2 is ready 3) ADC 1V9 enabled from FPGA 4) 2V5 and 3V3A enabled from FPGA. These shoud only be enabled after 1V9 is stable.
Note: 100 ohm resistor damps overshoot on power up. Recommended in ADC datasheet.
Note: 1V8 must be enabled before FPGA starts config process so that HSWAPEN is high and all FPGA pins are tri-stated.
